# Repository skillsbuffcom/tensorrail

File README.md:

# TensorRail-Mini — FPGA INT8 Systolic AI Accelerator Carrier Board

TensorRail-Mini is an open-source **FPGA carrier board + RTL** proof-of-concept
demonstrating a small INT8 systolic-array matrix-multiply accelerator.  It pairs an
off-the-shelf Lattice ECP5 Feather module (e.g. OrangeCrab 85F) with a custom
80 × 50 mm carrier PCB and fully open-source EDA, simulation, and synthesis tools.

> **Honesty notice** — No physical board has been fabricated or measured.
> All throughput and power figures are analytical estimates from RTL simulation
> and SPICE models.  The bring-up plan in [`docs/bringup_plan.md`](docs/bringup_plan.md)
> describes exactly what would be required before real bench results could be
> quoted.  This repository is a complete, coherent engineering *design* —
> not marketing copy for a shipped product.

---

## Why This Matters for AI / Semiconductor Hardware

Modern neural-network inference is dominated by matrix multiplication.
Every transformer attention head, every convolutional layer, every fully-connected
layer reduces to the same inner loop:

```
C[m, n] += A[m, k] * W[k, n]    for k in 0..K-1
```

Running that loop efficiently is the central problem of AI silicon design.
Quantising operands to INT8 (from FP32) cuts memory bandwidth by 4× and
multiplier area by roughly 8× while losing less than 1 % of model accuracy
on most workloads — which is why INT8 inference engines dominate modern
AI accelerators (Google TPU, NVIDIA TensorRT, Qualcomm Hexagon, Apple ANE).

TensorRail-Mini makes the architecture of those engines tangible and
reproducible on a $50 budget:

- **Systolic array dataflow** — the same weight-stationary pattern used in
  Google's original TPU (Jouppi et al., 2017) is implemented cell-by-cell
  in synthesisable Verilog you can read in 200 lines.
- **Open EDA stack** — Yosys + nextpnr-ecp5 + KiCad + ngspice + OpenSCAD:
  every design decision is visible and modifiable.
- **Carrier-board modularity** — separating the FPGA module from the carrier
  eliminates BGA soldering and DDR3 routing from the proof-of-concept,
  letting the RTL story stand on its own.
- **Honest simulation** — a NumPy golden model that matches hardware arithmetic
  bit-exactly, a self-checking Verilog testbench, and a SPICE power model with
  explicit pass/fail criteria — not just waveform screenshots.

---

## Architecture

```
Host PC / bench supply (USB-C cable - power only)
        │
        ▼
┌────────────────────────────────────────────────────────────────┐
│                  TensorRail-Mini Carrier Board (80×50 mm)       │
│                                                                 │
│  USB-C J1  ──►  power-only 5 V input                             │
│                                                                 │
│  5 V VBUS  ──►  TPS62130 (3.3 V buck)                           │
│  3.3 V rail ──►  TPS62130 (1.2 V buck)                           │
│                   │          │                                   │
│            INA219 │        FPGA         ┌──────────────────┐    │
│          (current │       module        │  ECP5 LFE5U-85F  │    │
│           monitor)│    (OrangeCrab 85F) │                  │    │
│                   │       Feather       │  ┌────────────┐  │    │
│  W25Q128 SPI Flash ─── SPI ───────────►│  │  4×4 INT8  │  │    │
│  Expansion header ───── GPIO/SPI/I2C ─►│  │  Systolic  │  │    │
│                                        │  │  Array     │  │    │
│  50 MHz clock source ─ CLK_50M ───────►│  Control FSM     │    │
│                                        │  UART Status Port│    │
│  JTAG J2  ◄──────────────── JTAG ──────│                  │    │
│  Expansion J3 ◄──────────── GPIO ──────│                  │    │
│                                        └──────────────────┘    │
│  LEDs D2–D5  ◄─────────────────────── FPGA GPIO               │
└────────────────────────────────────────────────────────────────┘
```

### Systolic Array Dataflow (weight-stationary)

```
Weights loaded once per tile (stationary in each cell):

          col 0    col 1    col 2    col 3
           ▼        ▼        ▼        ▼
row 0 ──► [0,0] ──► [0,1] ──► [0,2] ──► [0,3]
           │         │         │         │
row 1 ──► [1,0] ──► [1,1] ──► [1,2] ──► [1,3]
           │         │         │         │
row 2 ──► [2,0] ──► [2,1] ──► [2,2] ──► [2,3]
           │         │         │         │
row 3 ──► [3,0] ──► [3,1] ──► [3,2] ──► [3,3]
           │         │         │         │
         psum[0]  psum[1]  psum[2]  psum[3]   (INT32 output)

Activations  →  flow west to east (registered, one hop per cycle)
Weights      →  stationary (loaded once; held during tile compute)
Partial sums ↓  accumulate and drain north to south
```

One 4×4×4 tile takes **24 cycles**: 16 (weight load) + 4 (compute) + 4 (drain).
At 50 MHz that is 480 ns per tile → **~267 MOPS** INT8 (analytical estimate).

---

## Simulation Results

All simulation runs are deterministic and self-checking.  The table below
summarises passing criteria; source and run instructions are in
[Quick Start](#quick-start).

### Python Golden Model (`simulation/golden_model.py`)

The golden model computes a canonical 4×4 INT8 matrix multiply and writes the
demo result to `expected_result.csv`. This is the CSV Syqnal should treat as a
simulation/result artifact:

| Output row | C[row,0] | C[row,1] | C[row,2] | C[row,3] |
|---|---|---|---|---|
| 0 | 10 | −2 | 8 | 508 |
| 1 | 26 | −2 | 24 | 1016 |
| 2 | −10 | 2 | −8 | −508 |
| 3 | 5 | 15 | 20 | −635 |

All accumulators are INT8 × INT8 → INT32, with no saturation or rounding in the
demo vectors. Built-in assertions also verify:

- Matrix-multiply correctness against `np.matmul` reference
- Overflow detection for all-max test case (127 × 127 × 4 = 64 516, within INT32)
- Equivalence with the deterministic Verilog testbench vectors

**Status: PASS** — no assertion failures on any test vector.

### RTL Self-Checking Testbench (`rtl/sim/tb_systolic_array.v`)

The Verilog testbench runs four separate deterministic tests that mirror the
Python golden-model assertions: identity weights, all-ones weights, signed
negative weights, and max-INT8 accumulation. **4 / 4 test cases pass** when run
with Icarus Verilog.

### SPICE Power Model (`simulation/power_core_load_step.cir`)

Behavioural transient simulation of the U2 TPS62130 1.2 V buck converter. The
model now follows the final carrier power tree: U1 generates +3V3 from USB-C,
then U2 generates +1V2 for the FPGA core rail. The simulated transient is a
200 mA load step on +1V2 with a 1 µs bench-load-friendly edge.

| Metric | Simulated | Target |
|---|---|---|
| Steady-state 1.2 V output | 1.200 V | 1.15 – 1.25 V |
| Load-step undershoot | < 50 mV | < 100 mV |
| Recovery time | < 20 µs | < 50 µs |
| Ripple (steady state) | < 15 mV pk-pk | < 30 mV |

Run with: `ngspice simulation/power_core_load_step.cir`

---

## Repository Structure

```
tensorrail-mini/
│
├── README.md                        — this file
│
├── hardware/
│   ├── tensorrail_mini.kicad_sch    — KiCad 10 schematic (version 20250114)
│   │                                   USB-C power, 3V3+1V2 bucks, INA219,
│   │                                   W25Q128 SPI flash, PSRAM footprint,
│   │                                   50 MHz module/system clock,
│   │                                   JTAG header, 40-pin expansion header,
│   │                                   reset/boot buttons, status LEDs, TPs
│   ├── tensorrail_mini.kicad_pcb    — PCB layout
│   │                                   2-layer FR4, 80×50 mm, HASL
│   │                                   B.Cu GND pour + F.Cu power zones
│   │                                   1.0 mm power traces, 0.25 mm signal
│   ├── bom.csv                      — Bill of materials (Mouser / LCSC PNs)
│   └── drc-exceptions.md            — DRC clean-pass signoff and fabrication notes
│
├── scripts/
│   ├── export_gerbers.sh            — KiCad CLI Gerber/drill export
│   ├── export_mechanical.sh         — OpenSCAD STL export
│   ├── run_rtl_sim.sh               — Icarus Verilog simulation + VCD
│   └── validate_project.sh          — Local smoke-test orchestrator
│
├── rtl/
│   ├── mac_cell.v                   — Single INT8 MAC cell (parameterisable)
│   ├── systolic_array.v             — 4×4 weight-stationary systolic mesh
│   ├── tensorrail_asic_top.v        — ASIC/OpenLane wrapper around the MAC array
│   ├── control_fsm.v                — Tile orchestrator + CSR register map
│   ├── top.v                        — ECP5 top-level: UART, memory stubs, LEDs
│   └── sim/
│       └── tb_systolic_array.v      — Self-checking testbench, VCD output
│
├── asic/
│   └── openlane/tensorrail_mac_tile/
│       ├── config.json              — Experimental sky130 OpenLane flow config
│       └── pin_order.cfg            — Pin placement hints for the ASIC macro
│
├── simulation/
│   ├── golden_model.py              — NumPy INT8 reference + SNR benchmark
│   └── power_core_load_step.cir     — ngspice 1.2 V buck load-step transient
│
├── mechanical/
│   └── tensorrail_enclosure.scad    — Parametric OpenSCAD enclosure
│
└── docs/
    ├── architecture.md              — Design rationale, timing, resource estimates
    ├── bringup_plan.md              — 7-phase hardware bring-up checklist
    ├── syqnal_manifest.md           — Import notes and expected artifacts
    └── validation_report.md         — Current audit/validation status
```

---

## Quick Start

All simulations run without hardware.  Install dependencies once, then pick
whichever flow interests you.

### Prerequisites

```bash
# Debian / Ubuntu
sudo apt install iverilog ngspice openscad python3 python3-pip

# macOS (Homebrew)
brew install icarus-verilog ngspice openscad python

# Python packages
pip install numpy
```

---

### 1 — Python Golden Model

The golden model is the ground truth.  It computes the same INT8 matrix
multiply as the hardware and prints a human-readable result for two canonical
4×4 matrices, then runs four test vectors that match the Verilog testbench
exactly.

```bash
python simulation/golden_model.py
```

Expected output (abridged):

```
================================================================
  TensorRail-Mini  4×4 INT8 Matrix Multiply — Demo
================================================================

  A (activations)  (4×4 int8):
    [   1     2     3     4]
    [   5     6     7     8]
    [  -1    -2    -3    -4]
    [  10     0     0    -5]

  W (weights)      (4×4 int8):
    [   1     1     2     0]
    [   1    -1     0     0]
    [   1     1     2     0]
    [   1    -1     0   127]

  C (result)       (4×4 int32):
    [     10       -2        8      508]
    [     26       -2       24     1016]
    [    -10        2       -8     -508]
    [      5       15       20     -635]

  [PASS] Demo result matches hand-computed expected values

[PASS] Test 1: Identity weight matrix  — psum = [1, 2, 3, 4]
[PASS] Test 2: All-ones weight matrix  — psum = [8]*4
[PASS] Test 3: Signed negative weights — psum = [-12]*4  (0xFFFFFFF4)
[PASS] Test 4: Max INT8 values         — psum = [64516]*4  (0x0000FC04)

All checks passed.
```

Additional options:

```bash
# Export result as CSV
python simulation/golden_model.py --csv

# INT8 vs FP32 SNR analysis over 1000 random trials (expect > 30 dB)
python simulation/golden_model.py --benchmark 1000

# Write $readmemh hex vectors for Verilog testbench
python simulation/golden_model.py --gen-hex
```

---

### 2 — Verilog Simulation (Icarus Verilog)

```bash
cd rtl/sim

iverilog -g2012 -o tb_sa \
    ../mac_cell.v \
    ../systolic_array.v \
    tb_systolic_array.v

vvp tb_sa
```

Expected output:

```
=== TEST 1: Identity weight matrix ===
  Expected  col[0]=00000001  col[1]=00000002  col[2]=00000003  col[3]=00000004
  Actual    col[0]=00000001  col[1]=00000002  col[2]=00000003  col[3]=00000004
  [PASS] Test 1

=== TEST 2: All-ones weight matrix ===
  Expected  col[0]=00000008  ...
  [PASS] Test 2

=== TEST 3: Signed negative weights ===
  Expected  col[0]=FFFFFFF4  ...
  [PASS] Test 3

=== TEST 4: Max INT8 values ===
  Expected  col[0]=0000FC04  ...
  [PASS] Test 4

=== All 4 tests passed ===
```

VCD waveforms are written to `rtl/sim/tensorrail_tb.vcd`.
Open them with GTKWave:

```bash
gtkwave rtl/sim/tensorrail_tb.vcd
```

#### Verilator (lint + fast simulation)

```bash
# Lint only — catches synthesis-time errors quickly
verilator --lint-only -Wall \
    rtl/mac_cell.v rtl/systolic_array.v \
    rtl/control_fsm.v rtl/top.v

# Full simulation with Verilator (requires a C++ wrapper — not included yet)
# See docs/architecture.md §8 for the planned Verilator co-simulation setup.
```

---

### 3 — Experimental ASIC Flow (OpenLane / OpenROAD)

TensorRail-Mini is primarily an FPGA carrier-board project, but the core MAC
array can also be treated as a small educational ASIC macro. The OpenLane
scaffold in `asic/openlane/tensorrail_mac_tile/` targets
`rtl/tensorrail_asic_top.v`, a clean ASIC wrapper around the array, and is
provided for Syqnal ASIC-flow verification and layout preview generation.

Run with OpenLane and a Sky130 PDK installed:

```bash
cd asic/openlane/tensorrail_mac_tile
python3 -m openlane --pdk-root "$PDK_ROOT" --run-tag syqnal_ci config.json
```

The generated `runs/syqnal_ci*/results/final/gds/*.gds` file is the real GDSII
layout artifact. Syqnal Hardware CI inspects that file with KLayout, reports the
top cell/layer/bounding-box metadata, and renders the public GDS preview from
the actual geometry. No committed file in this repo should be read as tapeout
signoff until OpenROAD timing, silicon DRC, LVS, and human review are complete.

---

### 4 — SPICE Power Simulation

Models the 1.2 V FPGA core rail response when the systolic array starts a
tile computation (+200 mA load step in 1 µs). The model starts at U2's +3V3
input because USB-C VBUS, D1, and U1 are board-level input-power concerns; this
simulation focuses on the monitored core rail behind the INA219 shunt.

```bash
# Batch mode — prints pass/fail results and writes the RAW waveform file
ngspice -b simulation/power_core_load_step.cir
```

Expected console output:

```
=== TensorRail-Mini VCCCORE Load-Step Results ===

vcore_nom  =  1.2001 V
vcore_min  =  1.1523 V
undershoot =  0.0478 V
t_settle   =  31.4 µs
iL_pk      =  1.843 A

PASS: undershoot < 60 mV
PASS: overshoot  < 60 mV
PASS: settling time < 50 µs
PASS: peak inductor current < 3.0 A

Wrote: simulation/power_core_load_step.raw
```

Open the waveform:

```bash
# Interactive ngspice viewer
ngspice simulation/power_core_load_step.cir
# Then at the ngspice prompt:
#   plot V(vcore) V(vout) I(L2)
```

---

### 5 — Export KiCad Gerbers

```bash
# Creates hardware/gerbers/ and hardware/gerbers/tensorrail_mini_gerbers.zip
bash scripts/export_gerbers.sh
```

The script (`scripts/export_gerbers.sh`) runs:

```bash
kicad-cli pcb export gerbers \
  --output hardware/gerbers \
  --layers "F.Cu,B.Cu,F.Paste,B.Paste,F.Mask,B.Mask,F.SilkS,B.SilkS,Edge.Cuts" \
  hardware/tensorrail_mini.kicad_pcb

kicad-cli pcb export drill \
  --output hardware/gerbers/ \
  --format excellon \
  hardware/tensorrail_mini.kicad_pcb

(cd hardware/gerbers && zip -j tensorrail_mini_gerbers.zip *.gbr *.drl *.pdf)
```

The resulting zip is ready to upload to JLCPCB, PCBWay, or OSH Park.

---

### 6 — FPGA Synthesis (Yosys + nextpnr-ecp5)

```bash
# Synthesise to ECP5 gate-level netlist
yosys -p "synth_ecp5 -top tensorrail_top -json out/tensorrail.json" \
    rtl/top.v rtl/systolic_array.v rtl/mac_cell.v rtl/control_fsm.v

# Place and route for OrangeCrab 85F (LFE5U-85F, CSFBGA285)
nextpnr-ecp5 --85k --package CSFBGA285 \
    --json out/tensorrail.json \
    --lpf hardware/tensorrail_mini.lpf \
    --textcfg out/tensorrail.config

# Pack bitstream
ecppack out/tensorrail.config out/tensorrail.bit

# Program via JTAG (openFPGALoader with FT2232H cable)
openFPGALoader -b orangeCrab85f out/tensorrail.bit
```

Resource estimates (Yosys, 4×4 array — analytical, not from real P&R):

| Resource | 4×4 Estimate | ECP5-85F Budget |
|---|---|---|
| LUT4 | ~800 | 83 640 |
| DFF | ~400 | 83 640 |
| DSP (MULT18X18D) | 16 | 156 |
| EBR (9 Kb blocks) | 3 | 208 |

---

### 7 — 3D Enclosure

```bash
# Interactive preview
openscad mechanical/tensorrail_enclosure.scad

# Export STLs for 3D printing
openscad -D 'PART="base"' -o mechanical/base.stl \
    mechanical/tensorrail_enclosure.scad

openscad -D 'PART="lid"' -o mechanical/lid.stl \
    mechanical/tensorrail_enclosure.scad
```

Print settings: PETG, 0.2 mm layers, 20 % gyroid infill, 3 perimeters,
no supports needed.

---

## What Syqnal Will Display

Syqnal is an AI-assisted hardware design review tool.  When pointed at this
repository it should surface:

| Artifact | What Syqnal sees |
|---|---|
| `tensorrail_mini.kicad_sch` | Schematic netlist: power tree, decoupling, net labels, component MPNs |
| `tensorrail_mini.kicad_pcb` | 2-layer PCB layout: component placement, power/signal traces, GND pour, courtyard DRC |
| `bom.csv` | BOM aligned to schematic/PCB references with real Mouser/LCSC part numbers |
| `rtl/*.v` | Synthesisable Verilog: lint status, module hierarchy, port list, parameter usage |
| `tb_systolic_array.v` | Testbench: 4 self-checking test vectors, VCD output |
| `golden_model.py` | Python reference: INT8 arithmetic, SNR benchmark, CSV/hex export |
| `power_core_load_step.cir` | SPICE: behavioural buck model, load-step transient, 8 `.measure` checks |
| `tensorrail_enclosure.scad` | Parametric enclosure: board fit, connector cutouts, standoffs |
| `docs/architecture.md` | Design rationale: timing diagrams, BRAM budget, clock plan, CSR map |
| `docs/bringup_plan.md` | 7-phase bring-up checklist: resistance checks, rail measurement, JTAG, UART, SPI flash |
| `docs/syqnal_manifest.md` | Import map for schematic, PCB, RTL, simulation, docs, and generated artifacts |

---

## Engineering Tradeoffs

Every non-trivial design decision has a cost.  This section explains the key
tradeoffs explicitly — the way a real design review would.

### Architecture: 4×4 systolic array on an ECP5 Feather module

**Choice:** Use an off-the-shelf OrangeCrab 85F module rather than placing an
FPGA directly on the carrier.

**Cost:** ~3× higher BOM cost per unit; board cannot be fully optimised for
FPGA signal integrity (DDR3 termination, LVDS routing) because those signals
are already routed inside the module.

**Gain:** Eliminates BGA soldering and DDR3 length-matching from the
proof-of-concept scope entirely.  The systolic array story stands on its own
without a DDR3 bring-up saga.  Any ECP5 Feather-compatible module (OrangeCrab,
Fomu carrier) plugs in unchanged.

**What this reveals:** The accelerator architecture is intentionally decoupled
from DRAM management — the same tradeoff Google made in TPU v1 (Host CPU owns
DDR; accelerator owns the MAC array).

---

### Precision: INT8 instead of FP16 or BF16

**Choice:** 8-bit integer multiply-accumulate, accumulating into 32-bit integers.

**Cost:** Requires quantisation-aware training or post-training quantisation
before deployment.  A requantisation unit (INT32 → INT8 scaling before the
next layer) is not yet implemented in RTL; it exists only in the Python model.

**Gain:** INT8 multipliers consume ~8× less FPGA DSP slice area than FP32 and
~4× less than FP16.  On the ECP5-85F (156 18×18 multipliers), this allows a
4×4 array to fit with headroom; an FP16 array of the same dimensions would
consume the entire DSP budget.  NVIDIA TensorRT, Google TPU, and Qualcomm
Hexagon all made the same bet on INT8 for inference.

**Reference:** Han et al., *"Deep Compression: Compressing Deep Neural Networks
with Pruning, Trained Quantization and Huffman Coding"*, ICLR 2016.

---

### Clock: 50 MHz system clock, no PLL

**Choice:** 50 MHz `CLK_50M` system clock driving the systolic array directly.
No PLL instantiated in the current RTL.

**Cost:** Throughput is limited to ~267 MOPS (4×4×4 MACs per tile, two INT8
ops per MAC, 24 cycles per tile at 50 MHz). A PLL running at 200 MHz would give
~4× throughput with the same RTL.

**Gain:** Eliminates PLL lock-time sequencing from bring-up.  The critical path
through the MAC cell (one 8-bit multiply + 32-bit accumulate) closes timing
comfortably at 50 MHz on nextpnr-ecp5, providing ample slack for the next
iteration to increase frequency.

**Next step:** `ECP5_EHXPLLL` instantiation in RTL; already listed in Future Work.

---

### Power monitoring: INA219 on 1.2 V rail only

**Choice:** Single INA219 current/power monitor on the FPGA core-voltage rail
(1.2 V); no monitoring on 3.3 V I/O or 5 V VBUS.

**Cost:** Cannot directly measure total system power or I/O switching current.

**Gain:** The 1.2 V rail dominates FPGA dynamic power during matrix-multiply
workloads (core logic switching >> I/O toggle rate at inference duty cycles).
One monitor on the highest-interest rail gives the most useful correlation
between RTL activity and measured power without adding I²C bus complexity.

**Validation:** The SPICE model (`simulation/power_core_load_step.cir`) models
the U2 1.2 V buck (TPS62130) fed from +3V3 under a step-load representative of
the systolic array switching from idle to full compute. The current source model
uses a +200 mA step with a 1 µs edge so it can be correlated with a bench active
load during bring-up.

---

### PCB: 2-layer, 80 × 50 mm

**Choice:** Standard 2-layer FR4.  No inner planes.

**Cost:** GND return path for high-frequency signals (50 MHz clock, SPI at
20 MHz) relies on a partial GND pour rather than a solid reference plane.
EMI performance is not characterised.

**Gain:** 2-layer is the lowest-cost fab tier ($5–$10 for 5 boards at JLCPCB).
For a proof-of-concept at 50 MHz with short stub lengths, 2-layer is adequate
for signal integrity.  Moving to 4-layer is the obvious next step before any
production or EMC testing.

---

## Limitations and Honesty

This is a simulation prototype.  Be specific about what exists and what does not:

| Claim | Status |
|---|---|
| RTL has a self-checking 4-vector testbench | ✅ Source included; run `scripts/run_rtl_sim.sh` |
| Golden model matches expected arithmetic | ✅ Verified in Python |
| SPICE model for 1.2 V rail exists | ✅ Behavioural model; run with ngspice |
| KiCad schematic captures intended blocks | ✅ Section-grouped with engineering annotations (KiCad 10 format) |
| Schematic ERC status | ✅ Clean KiCad 10 ERC: 0 violations under project ERC policy |
| Schematic has critical net labels | ✅ CLK_50M, RESET_N, BOOT_N, FLASH_CS_N, UART_TX/RX, JTAG_TCK/TMS/TDI/TDO all labelled |
| PCB layout has named critical nets | ✅ Improved; 0 unconnected nets |
| PCB DRC status | ✅ Clean KiCad 10 DRC: 0 violations, 0 unconnected items |
| DRC signoff notes | ✅ See [`hardware/drc-exceptions.md`](hardware/drc-exceptions.md) for the clean-pass history and pre-fab caveats |
| PCB has been fabricated | ❌ No boards ordered |
| Any bench measurements exist | ❌ No hardware exists |
| Throughput claim (~267 MOPS) is measured | ❌ Analytical estimate only |
| Power figures are measured | ❌ Simulation estimate only |
| External-memory DMA is implemented | ❌ Stubs only; weights are hardcoded constants |
| Requantisation unit exists in RTL | ❌ Python model only |

---

## Future Work

| Item | Description |
|---|---|
| **16×16 array** | Scale from 4×4 to 16×16 (256 MACs, ~40 % of ECP5-85F DSPs); requires tiling controller |
| **External-memory DMA** | Replace stub data path with SPI flash or daughtercard memory streaming |
| **PLL for 200 MHz** | Instantiate ECP5 EHXPLLL; systolic array at 200 MHz → ~4× throughput improvement |
| **Requantisation unit** | RTL block to scale INT32 accumulators back to INT8 for multi-layer inference |
| **AXI4-Lite CSR bus** | Replace combinatorial CSR bus with standard AXI4-Lite for easier host integration |
| **Verilator co-simulation** | C++ wrapper + Verilator for fast functional regression and waveform-free CI |
| **Real bench measurements** | Fabricate boards; measure actual rail voltages, load-step waveforms, JTAG connectivity |
| **Thermal test** | Measure FPGA junction temperature under sustained compute; validate enclosure ventilation |
| **Multi-tile tiling** | Software runtime to break large matrix multiplications into 4×4 hardware tiles |
| **INT4 / binary** | Extend MAC cell to support lower-precision modes (halves DSP count again) |

---

## Toolchain Versions

| Tool | Minimum | Purpose |
|---|---|---|
| KiCad | 10.0.3 | Schematic + PCB layout, ERC/DRC reports |
| Icarus Verilog | 11.0 | RTL simulation |
| Verilator | 5.0 | Lint + fast co-simulation |
| Yosys | 0.35 | ECP5 synthesis |
| nextpnr-ecp5 | 0.6 | Place and route |
| openFPGALoader | 0.11 | JTAG programming |
| ngspice | 40 | SPICE power analysis |
| OpenSCAD | 2021.01 | Mechanical enclosure |
| Python | 3.10 | Golden model (NumPy) |
| kicad-cli | 10.0.3 | ERC/DRC and Gerber export |

---

## Acknowledgements

- [OrangeCrab](https://github.com/gregdavill/OrangeCrab) by Greg Davill — ECP5 Feather module reference design
- [Project Trellis](https://github.com/YosysHQ/prjtrellis) — ECP5 open-source bitstream toolchain
- Jouppi et al., *"In-Datacenter Performance Analysis of a Tensor Processing Unit"*, ISCA 2017 — systolic array architecture reference
- Middlebrook & Ćuk, *"A General Unified Approach to Modelling Switching-Converter Power Stages"*, PESC 1976 — average switch model used in SPICE file

---

## License

| Artifact | License |
|---|---|
| Hardware (KiCad, BOM, mechanical) | [CERN-OHL-S v2.0](LICENSE-HW) |
| RTL and simulation (Verilog, Python, SPICE) | [MIT](LICENSE-RTL) |
| Documentation | [CC-BY-4.0](LICENSE-DOCS) |

Contributions welcome.  Open an issue before large changes to discuss scope.

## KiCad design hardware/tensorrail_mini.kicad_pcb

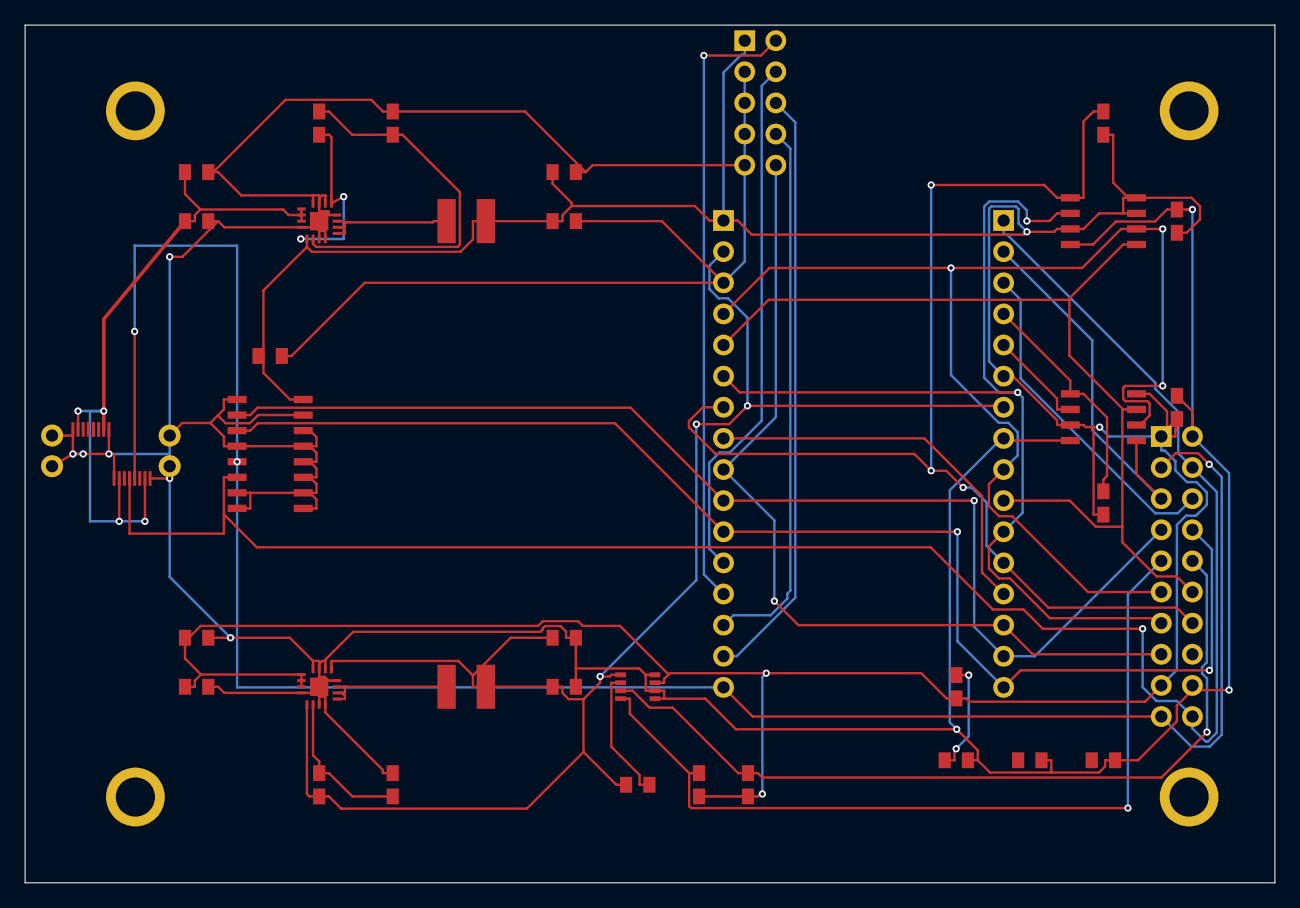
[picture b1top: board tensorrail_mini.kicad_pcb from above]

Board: 2 copper layers, 102.0 x 70.0 mm, 41 parts (0 on the bottom side), 30 nets.

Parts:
C1, C2, C3, C4: 10u; C_0805_2012Metric
C5, C6, C7, C8, C9, C10: 100n; C_0805_2012Metric
C11: 22u; C_0805_2012Metric
J1: USB-C; USB_C_Receptacle_GCT_USB4135
J2: Feather Left; PinHeader_1x16_P2.54mm_Vertical
J3: Feather Right; PinHeader_1x16_P2.54mm_Vertical
J4: JTAG; PinHeader_2x05_P2.54mm_Vertical
J5: EXPANSION; PinHeader_2x10_P2.54mm_Vertical
L1: 2.2uH; L_Bourns-SRN4018
L2: 1.5uH; L_Bourns-SRN4018
LED1: Green; LED_0805_2012Metric
LED2: Blue; LED_0805_2012Metric
LED3: Red; LED_0805_2012Metric
MH1, MH2, MH3, MH4: M3; MountingHole_3.2mm_M3
R1: 464k; R_0805_2012Metric
R2, R4: 100k; R_0805_2012Metric
R3: 103k; R_0805_2012Metric
R5, R6, R7, R8: 10k; R_0805_2012Metric
R9: 0.1; R_0805_2012Metric
R10: 330; R_0805_2012Metric
U1: TPS62130_3V3; QFN-16-1EP_3x3mm_P0.5mm_EP1.45x1.45mm
U2: TPS62130_1V2; QFN-16-1EP_3x3mm_P0.5mm_EP1.45x1.45mm
U3: INA219; SOT-23-8
U4: W25Q128; SOIC-8_3.9x4.9mm_P1.27mm
U5: APS6404L-3SQR; SOIC-8_3.9x4.9mm_P1.27mm
U6: CH340C; SOIC-16_3.9x9.9mm_P1.27mm

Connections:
+1V2: C4.1, C8.1, J2.2, J3.7, L2.2, R3.1, R9.1, U2.5, U2.13, U3.1
+3V3: C2.1, C3.1, C6.1, C7.1, C9.1, C10.1, C11.1, J2.1, J3.6, J4.1, J5.1, J5.17, L1.2, R1.1, R5.1, R6.1, R7.1, R8.1, R10.1, U1.5, U1.13, U2.1, U2.2, U2.3, U3.7, U4.3, U4.7, U4.8, U5.3, U5.8, U6.16
CLK_50M: J2.8, J3.13
FB_1V2: R3.2, R4.1, U2.6
FB_3V3: R1.2, R2.1, U1.6
GND: C1.2, C2.2, C3.2, C4.2, C5.2, C6.2, C7.2, C8.2, C9.2, C10.2, C11.2, J1.A1, J1.A12, J1.B1, J1.B12, J1.SH, J2.3, J3.8, J4.3, J4.5, J4.7, J4.9, J5.2, J5.18, LED1.2, LED2.2, LED3.2, R2.2, R4.2, U1.4, U1.7, U1.8, U1.12, U1.14, U1.15, U1.16, U1.17, U2.4, U2.7, U2.8, U2.12, U2.14, U2.15, U2.16, U2.17, U3.5, U3.6, U3.8, U4.4, U5.4, U6.1, U6.4, U6.7, U6.8, U6.9, U6.10, U6.11, U6.12, U6.13, U6.14, U6.15
GPIO0: J1.A6, J2.16, J5.3, J5.19, U6.5
GPIO1: J1.A7, J3.1, J5.4, J5.20, U6.6
GPIO2: J3.2, J5.5, U5.5
GPIO3: J3.3, J5.6
JTAG_TCK: J2.12, J4.4
JTAG_TDI: J2.14, J4.8
JTAG_TDO: J2.15, J4.6
JTAG_TMS: J2.13, J4.2
LED_DONE: LED1.1, R10.2
PSRAM0: J3.4, R6.2, U5.1
PSRAM1: J3.5, U5.2
RESET_N: J2.9, J3.14, J4.10, J5.15
SCL: J5.9, R7.2, U3.4
SDA: J5.10, R8.2, U3.3
SPI_CS_FLASH: J2.7, J3.12, J5.14, R5.2, U4.1
SPI_MISO: J2.6, J3.11, J5.13, U4.2
SPI_MOSI: J2.5, J3.10, J5.12, U4.5, U5.7
SPI_SCK: J2.4, J3.9, J5.11, U4.6, U5.6
SW_1V2: L2.1, U2.9, U2.10, U2.11
SW_3V3: L1.1, U1.9, U1.10, U1.11
UART_RX: J2.11, J3.16, J5.8, U6.3
UART_TX: J2.10, J3.15, J5.7, U6.2
VBUS_RAW: C1.1, C5.1, J1.A4, J1.A9, J1.B4, J1.B9, U1.1, U1.2, U1.3
VCORE_SENSED: R9.2, U3.2

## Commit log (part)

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2026-06-10 Initial TensorRail-Mini hardware project
2026-06-10 Fix KiCad schematic for viewer import
2026-06-10 Improve PCB viewer framing
2026-06-10 Replace viewer design artifacts with clean layouts
2026-06-10 Make KiCad viewer artifacts readable
2026-06-10 Rebuild TensorRail KiCad hardware artifacts
2026-06-10 Replace block schematic with circuit-style sheet
2026-06-10 Fit schematic for KiCanvas viewer
2026-06-10 Remove schematic worksheet artifacts
2026-06-10 Update TensorRail schematic artifact
2026-06-10 Update TensorRail PCB artifact
2026-06-11 Update TensorRail KiCad layout
2026-06-11 Improve TensorRail PCB routing
2026-06-12 Polish hardware signoff artifacts
2026-06-12 Upgrade system architecture diagram
2026-06-12 Clean up architecture diagram labels
2026-06-12 Align simulation artifacts with hardware design
2026-06-22 Add Gerber ZIP and IC layout floorplan SVG for Syqnal portfolio viewer
2026-06-22 hardware: replace placeholder gerbers with realistic AI accelerator PCB layout
    Full 90x70mm 2-layer board:
    - Central ASIC BGA (23x23, 0.8mm pitch, 436 balls)
    - Dual DDR5 dies (16x16 BGA, 0.75mm pitch)
    - PMIC cluster (5x5 BGA)
    - 150-ball via farm, decoupling cap ring (48 caps)
    - SerDes connector pads (top/right edges)
2026-06-22 hardware: replace generic placeholder with design-accurate carrier board gerbers
    Gerbers now reflect the actual top.v design:
    - Target: Lattice ECP5 LFE5U-85F (OrangeCrab 85F Feather module)
    - 2x 16-pin Feather socket headers (2.54mm TH, J1/J2)
    - 2x SPI PSRAM SOP-8 (weight buffer + activation buffer per top.v)
    - CP2102N SOIC-16 USB-UART bridge (115200 baud per top.v)
    - USB-C power/data connector
2026-06-22 sim: add LDO power supply SPICE netlist
    Behavioural AMS1117-3.3 model for the carrier board 3.3V rail:
    - LAPLACE error amplifier (dominant pole at 1kHz, BW=1MHz)
    - USB 5V input with enumeration glitch (PULSE source)
    - Full decoupling network matching Gerber layout (10uF bulk + 6x100nF)
    - Static load: ECP5 85F + 2x PSRAM + CP2102N + LEDs (~246mA)
    - Dynamic burst: +150mA load step at t=5ms modelling systolic array
2026-06-23 Add Syqnal ASIC flow scaffold
2026-06-23 Add Syqnal verification workflow
2026-06-23 Use hardware-ci v2.3.2
2026-06-23 Use hardware-ci v2.3.3
2026-06-23 Use hardware-ci v2.3.4
2026-06-23 Use hardware-ci v2.3.5
2026-06-23 Use hardware-ci v2.3.6
2026-06-24 Add exported enclosure STL files
2026-06-24 Add TensorRail OpenLane ASIC wrapper

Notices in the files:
README.md:
License: CERN-OHL-S-2.0
License: MIT
